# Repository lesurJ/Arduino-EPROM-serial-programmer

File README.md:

# Arduino-EPROM-serial-programmer

A project to program vintage EPROMs with modern Python and Arduino.

/!\ Work in progress. New version will include voltage regulators to generate the required programming voltages.

## Introduction

EPROMs are found in many old devices (scopes, data logger, computer). They are very good at long term data retention. And the good thing is they can be erased and re-programmed easily (with a bit of hardware).

Unfortunately, the devices for reading and programming EPROMs are usually expensive as they are universal: they can program almost all EPROMs. I really don't need such universal programmers as I use EPROMs for my hobby and I have only a few different types of EPROM.

## Description

A serial connection is opened between the computer and the arduino. This connection is used to transfer commands (read or write) and data (memory contents or machine code).

The circuit schematic is located [here](EPROM_FLASHER/Schematic.pdf).
It is based on an Arduino Nano, two 8-bit serial-in parallel-out shift registers (ref. 74HC595) and some passive components (condensator, 3 capacitors, 3 switches). Two soldering pads are present for powering the "program pin" of the EPROMs during a write operation.

The address lines of the EPROMs are driven by the shift registers whereas their data lines are driven by 8 Arduino pins.

## Installation

* Flash the [arduino program](arduino_programmer/arduino_programmer.ino) into the Arduino Nano. Use the Arduino IDE for this.
* Get yourself the PCB. You can directly upload the [zip file](EPROM_FLASHER/GERBER/EPROM_FLASHER.zip) to PCB production services.
* Solder the components on the PCB.
* Install a SINGLE EPROM on the board.

## Usage

* Connect the Arduino to the computer.
* For reading the EPROM run

```sh
python3 main.py -t X
```

where **X** is the memory type code (see [supported EPROMs](#supported-eproms)). The EPROM contents will be written in the file [epromContents_before.txt](epromContents_before.txt).

* For programming the EPROM run

```python
python3 main.py -t X -f path-to-the-machine-code-txt
```

where **X** is the memory type code (see [supported EPROMs](#supported-eproms)) and the path is indicating where you machine code is located.
Before programming, the program will pause and ask you to apply the programming voltage on the external supply pad. It will resume once you press the ENTER key.

## Example

A machine code example is located [here](programs/machineCode.txt). It is not a binary file but a txt files containing the program bytes on separate lines.

&rarr; If I want to read the contents of a NEC 2732D EPROM, I run

```sh
python3 main.py -t 32
```

&rarr; If I want to write the program [programs/machineCode.txt](programs/machineCode.txt) in the NEC 2732D EPROM, I run

```sh
python3 main.py -t 32 -f programs/machineCode.txt
```

I can see the contents of the EPROM in the file [epromContents_before.txt](epromContents_before.txt).

## Supported EPROMs

|EPROM|memory code|Memory Size [bytes]|
|---|---|---|
|27x16|16|2048|
|27x32|32|4096|
|27x64|64|8192|
|27x128|128|16384|
|27x256|256|32768|
|27x512|512|65536|

## Warning

DO NOT HOT-SWAP EPROM!

READ CAREFULLY THE DATASHEET FOR YOUR EPROM TO CHECK THE PROGRAMMING PROCEDURE AND VOLTAGE!

## Note

This project was made with components I had laying around. I didn't have a ZIF (Zero Insertion Force) socket for the EPROMs and this is the reason why I used 6 different sockets.

To keep the board simple, the programming voltage is not generated on the board, but  by an external power supply whose wires are attached to the power supply terminals.

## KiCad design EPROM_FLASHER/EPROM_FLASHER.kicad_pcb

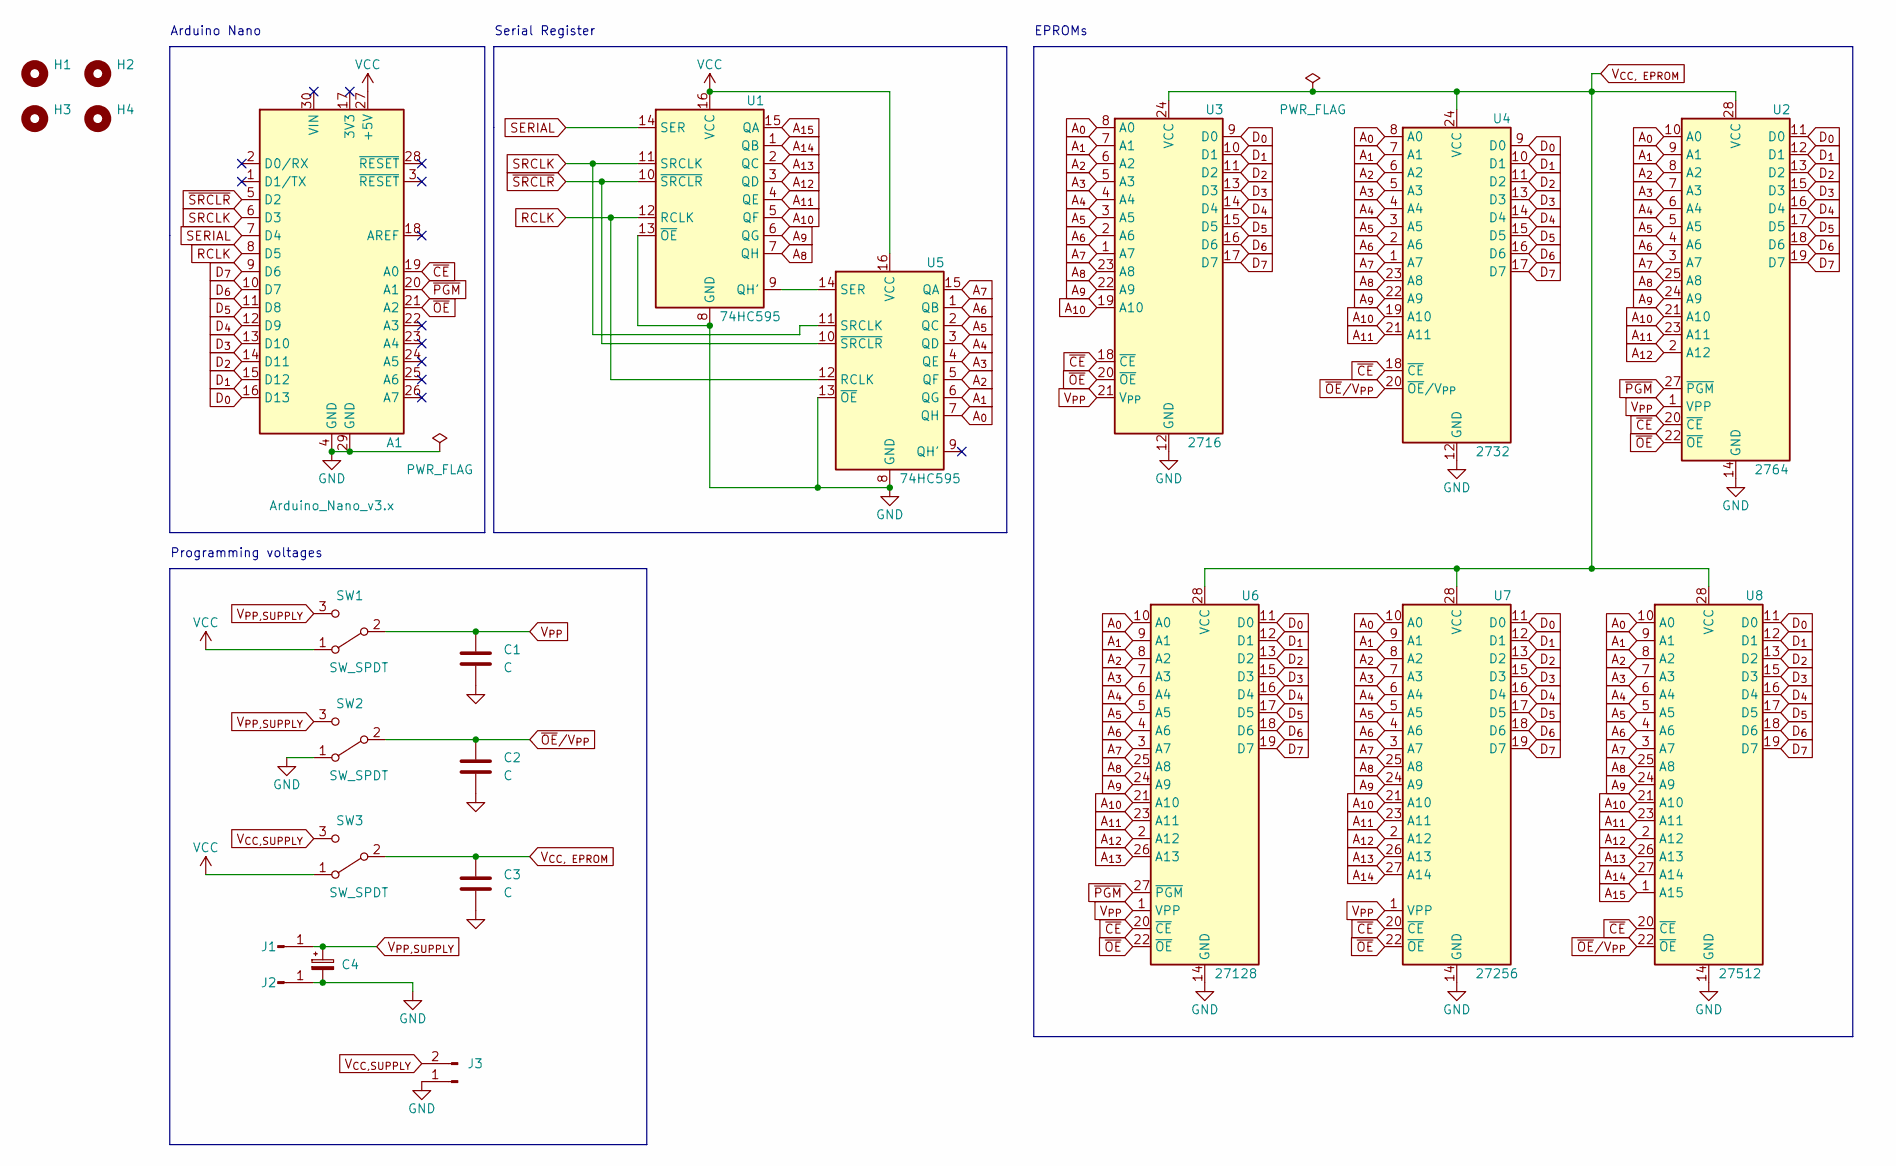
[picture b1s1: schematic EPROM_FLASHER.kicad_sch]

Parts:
A1: Arduino_Nano_v3.x; Arduino_Nano
C1, C2, C3: C; C_Disc_D9.0mm_W2.5mm_P5.00mm
C4: C_Polarized_Small; CP_Radial_D8.0mm_P3.50mm
H1, H2, H3, H4: MountingHole; MountingHole_2.2mm_M2
J1, J2: Conn_01x01_Male; TestPoint_Pad_4.0x4.0mm
J3: Conn_01x02_Male; PinHeader_1x02_P2.54mm_Vertical
SW1, SW2, SW3: SW_SPDT; SPDT_p2.54mm
U1, U5: 74HC595; DIP-16_W7.62mm
U2: 2764; DIP-28_W15.24mm
U3: 2716; DIP-24_W15.24mm
U4: 2732; DIP-24_W15.24mm
U6: 27128; DIP-28_W15.24mm
U7: 27256; DIP-28_W15.24mm
U8: 27512; DIP-28_W15.24mm

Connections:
A_{0}: U2.10 (A0), U3.8 (A0), U4.8 (A0), U5.7 (QH), U6.10 (A0), U7.10 (A0), U8.10 (A0)
A_{1}: U2.9 (A1), U3.7 (A1), U4.7 (A1), U5.6 (QG), U6.9 (A1), U7.9 (A1), U8.9 (A1)
A_{2}: U2.8 (A2), U3.6 (A2), U4.6 (A2), U5.5 (QF), U6.8 (A2), U7.8 (A2), U8.8 (A2)
A_{3}: U2.7 (A3), U3.5 (A3), U4.5 (A3), U5.4 (QE), U6.7 (A3), U7.7 (A3), U8.7 (A3)
A_{4}: U2.6 (A4), U3.4 (A4), U4.4 (A4), U5.3 (QD), U6.6 (A4), U7.6 (A4), U8.6 (A4)
A_{5}: U2.5 (A5), U3.3 (A5), U4.3 (A5), U5.2 (QC), U6.5 (A5), U7.5 (A5), U8.5 (A5)
A_{6}: U2.4 (A6), U3.2 (A6), U4.2 (A6), U5.1 (QB), U6.4 (A6), U7.4 (A6), U8.4 (A6)
A_{7}: U2.3 (A7), U3.1 (A7), U4.1 (A7), U5.15 (QA), U6.3 (A7), U7.3 (A7), U8.3 (A7)
A_{8}: U1.7 (QH), U2.25 (A8), U3.23 (A8), U4.23 (A8), U6.25 (A8), U7.25 (A8), U8.25 (A8)
A_{9}: U1.6 (QG), U2.24 (A9), U3.22 (A9), U4.22 (A9), U6.24 (A9), U7.24 (A9), U8.24 (A9)
A_{10}: U1.5 (QF), U2.21 (A10), U3.19 (A10), U4.19 (A10), U6.21 (A10), U7.21 (A10), U8.21 (A10)
A_{11}: U1.4 (QE), U2.23 (A11), U4.21 (A11), U6.23 (A11), U7.23 (A11), U8.23 (A11)
A_{12}: U1.3 (QD), U2.2 (A12), U6.2 (A12), U7.2 (A12), U8.2 (A12)
A_{13}: U1.2 (QC), U6.26 (A13), U7.26 (A13), U8.26 (A13)
A_{14}: U1.1 (QB), U7.27 (A14), U8.27 (A14)
A_{15}: U1.15 (QA), U8.1 (A15)
D_{0}: A1.16 (D13), U2.11 (D0), U3.9 (D0), U4.9 (D0), U6.11 (D0), U7.11 (D0), U8.11 (D0)
D_{1}: A1.15 (D12), U2.12 (D1), U3.10 (D1), U4.10 (D1), U6.12 (D1), U7.12 (D1), U8.12 (D1)
D_{2}: A1.14 (D11), U2.13 (D2), U3.11 (D2), U4.11 (D2), U6.13 (D2), U7.13 (D2), U8.13 (D2)
D_{3}: A1.13 (D10), U2.15 (D3), U3.13 (D3), U4.13 (D3), U6.15 (D3), U7.15 (D3), U8.15 (D3)
D_{4}: A1.12 (D9), U2.16 (D4), U3.14 (D4), U4.14 (D4), U6.16 (D4), U7.16 (D4), U8.16 (D4)
D_{5}: A1.11 (D8), U2.17 (D5), U3.15 (D5), U4.15 (D5), U6.17 (D5), U7.17 (D5), U8.17 (D5)
D_{6}: A1.10 (D7), U2.18 (D6), U3.16 (D6), U4.16 (D6), U6.18 (D6), U7.18 (D6), U8.18 (D6)
D_{7}: A1.9 (D6), U2.19 (D7), U3.17 (D7), U4.17 (D7), U6.19 (D7), U7.19 (D7), U8.19 (D7)
GND: A1.4 (GND), A1.29 (GND), C1.2, C2.2, C3.2, C4.2, J2.1, J3.1, SW2.1 (A), U1.8 (GND), U1.13 (~OE), U2.14 (GND), U3.12 (GND), U4.12 (GND), U5.8 (GND), U5.13 (~OE), U6.14 (GND), U7.14 (GND), U8.14 (GND)
unnamed: U1.9 (QH'), U5.14 (SER)
RCLK: A1.8 (D5), U1.12 (RCLK), U5.12 (RCLK)
SERIAL: A1.7 (D4), U1.14 (SER)
SRCLK: A1.6 (D3), U1.11 (SRCLK), U5.11 (SRCLK)
VCC: A1.27 (+5V), SW1.1 (A), SW3.1 (A), U1.16 (VCC), U5.16 (VCC)
V_{CC, EPROM}: C3.1, SW3.2 (B), U2.28 (VCC), U3.24 (VCC), U4.24 (VCC), U6.28 (VCC), U7.28 (VCC), U8.28 (VCC)
V_{CC,SUPPLY}: J3.2, SW3.3 (C)
V_{PP,SUPPLY}: C4.1, J1.1, SW1.3 (C), SW2.3 (C)
V_{PP}: C1.1, SW1.2 (B), U2.1 (VPP), U3.21 (V_{PP}), U6.1 (VPP), U7.1 (VPP)
~CE: A1.19 (A0), U2.20 (~CE), U3.18 (~CE), U4.18 (~CE), U6.20 (~CE), U7.20 (~CE), U8.20 (~CE)
~OE: A1.21 (A2), U2.22 (~OE), U3.20 (~OE), U6.22 (~OE), U7.22 (~OE)
~OE/V_{PP}: C2.1, SW2.2 (B), U4.20 (~OE/V_{PP}), U8.22 (~OE)
~PGM: A1.20 (A1), U2.27 (~PGM), U6.27 (~PGM)
~SRCLR: A1.5 (D2), U1.10 (~SRCLR), U5.10 (~SRCLR)

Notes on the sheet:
EPROMs
Serial Register
Programming voltages
Arduino Nano

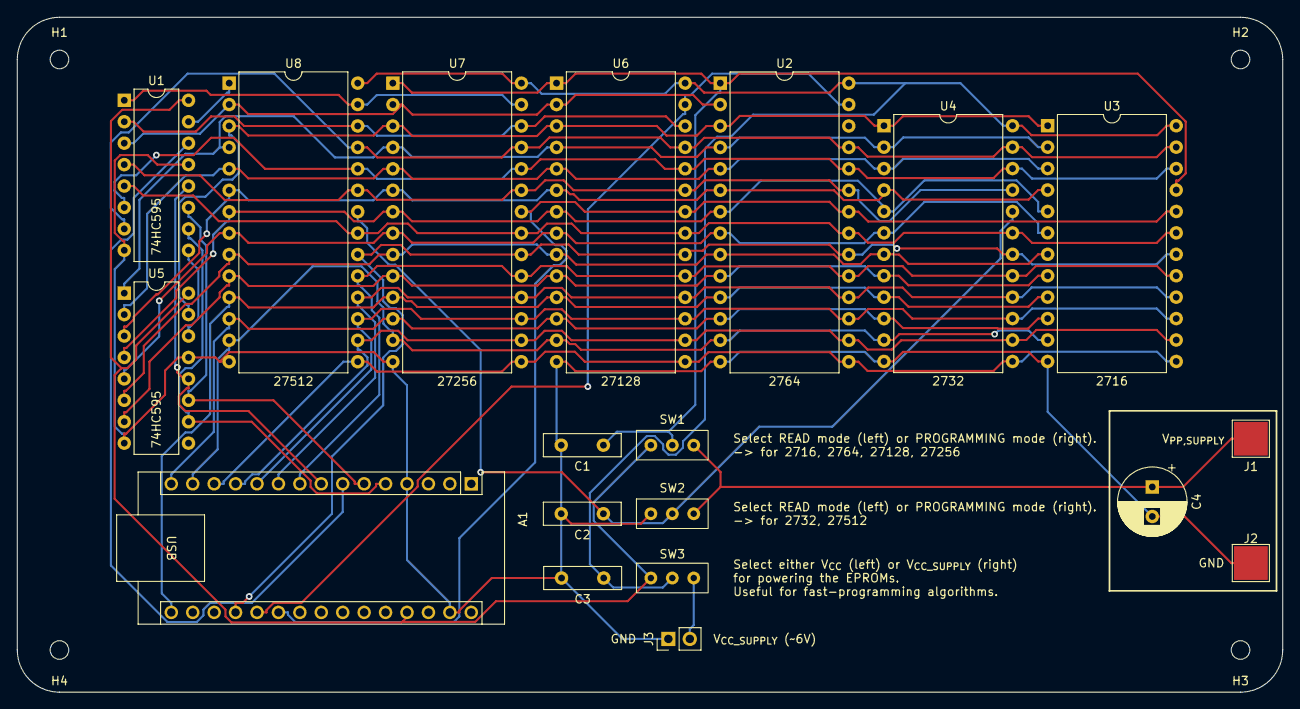
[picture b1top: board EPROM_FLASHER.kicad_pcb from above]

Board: 2 copper layers, 150.0 x 80.0 mm, 23 parts (0 on the bottom side), 39 nets.

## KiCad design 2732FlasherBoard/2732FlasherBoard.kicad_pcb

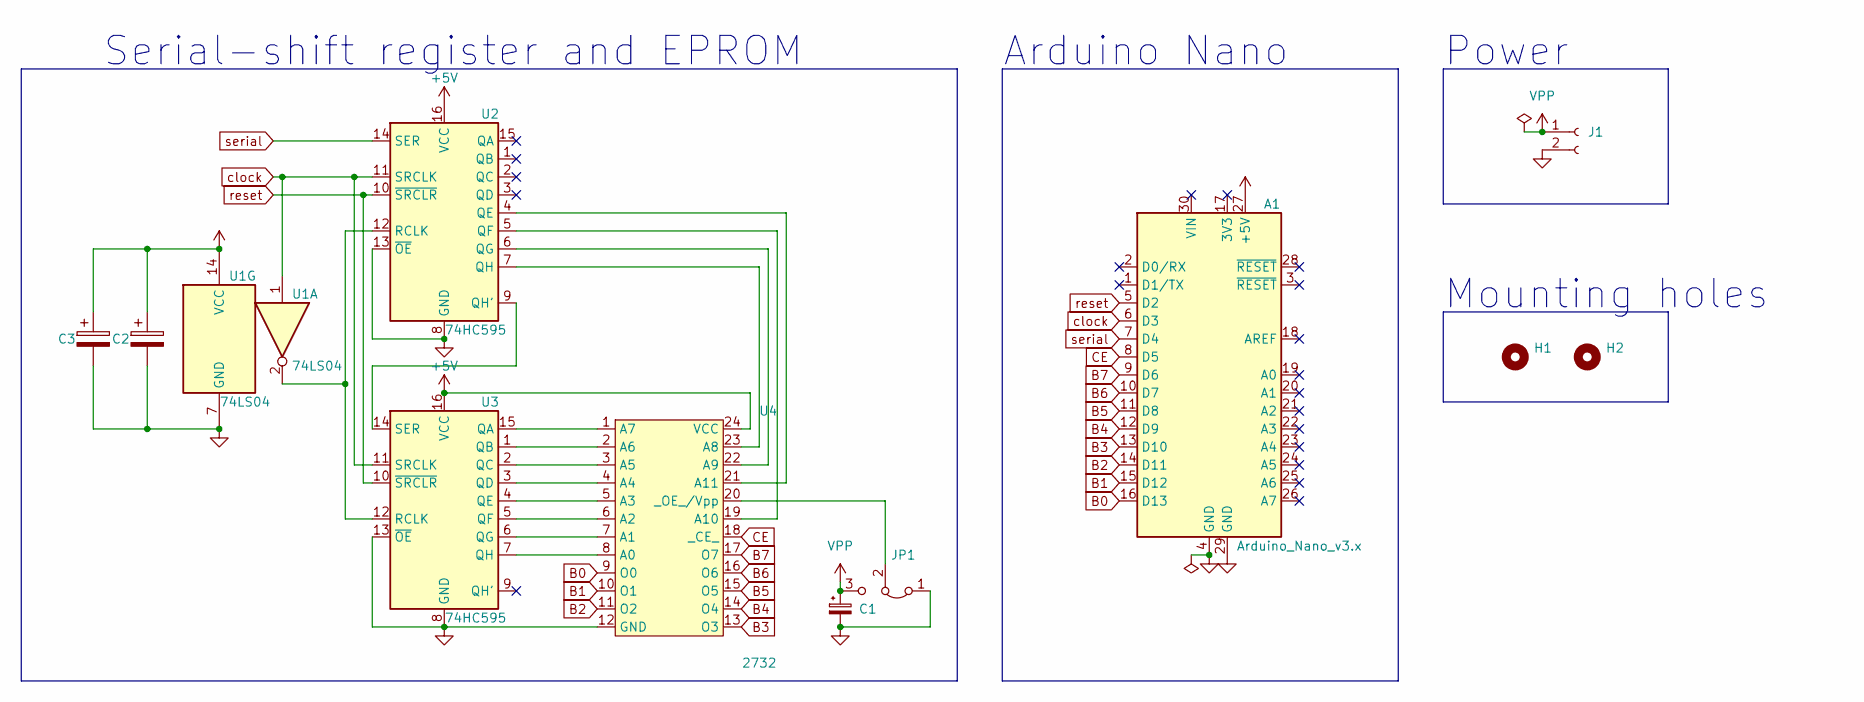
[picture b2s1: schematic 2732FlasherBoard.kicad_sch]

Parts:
A1: Arduino_Nano_v3.x; Arduino_Nano
C1: C_Polarized_Small; CP_Radial_D5.0mm_P2.00mm
C2, C3: C_Polarized; CP_Radial_D8.0mm_P3.50mm
H1, H2: MountingHole; MountingHole_2.5mm
J1: Conn_01x02_Female; PinHeader_1x02_P2.54mm_Vertical
JP1: Jumper_3_Bridged12; PinHeader_1x03_P2.54mm_Vertical
U1: 74LS04; DIP-14_W7.62mm
U2, U3: 74HC595; DIP-16_W7.62mm
U4: 2732; DIP-24_W15.24mm_Socket

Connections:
+5V: A1.27 (+5V), C2.1, C3.1, U1.14 (VCC), U2.16 (VCC), U3.16 (VCC), U4.24 (VCC)
B0: A1.16 (D13), U4.9 (O0)
B1: A1.15 (D12), U4.10 (O1)
B2: A1.14 (D11), U4.11 (O2)
B3: A1.13 (D10), U4.13 (O3)
B4: A1.12 (D9), U4.14 (O4)
B5: A1.11 (D8), U4.15 (O5)
B6: A1.10 (D7), U4.16 (O6)
B7: A1.9 (D6), U4.17 (O7)
CE: A1.8 (D5), U4.18 (_CE_)
GND: A1.4 (GND), A1.29 (GND), C1.2, C2.2, C3.2, J1.2, JP1.1 (A), U1.7 (GND), U2.8 (GND), U2.13 (~OE), U3.8 (GND), U3.13 (~OE), U4.12 (GND)
unnamed: JP1.2 (C), U4.20 (_OE_/Vpp)
unnamed: U1.2, U2.12 (RCLK), U3.12 (RCLK)
unnamed: U2.4 (QE), U4.21 (A11)
unnamed: U2.5 (QF), U4.19 (A10)
unnamed: U2.6 (QG), U4.22 (A9)
unnamed: U2.7 (QH), U4.23 (A8)
unnamed: U2.9 (QH'), U3.14 (SER)
unnamed: U3.1 (QB), U4.2 (A6)
unnamed: U3.2 (QC), U4.3 (A5)
unnamed: U3.3 (QD), U4.4 (A4)
unnamed: U3.4 (QE), U4.5 (A3)
unnamed: U3.5 (QF), U4.6 (A2)
unnamed: U3.6 (QG), U4.7 (A1)
unnamed: U3.7 (QH), U4.8 (A0)
unnamed: U3.15 (QA), U4.1 (A7)
VPP: C1.1, J1.1, JP1.3 (B)
clock: A1.6 (D3), U1.1, U2.11 (SRCLK), U3.11 (SRCLK)
reset: A1.5 (D2), U2.10 (~SRCLR), U3.10 (~SRCLR)
serial: A1.7 (D4), U2.14 (SER)

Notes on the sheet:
Arduino Nano
Power
Mounting holes
Serial-shift register and EPROM

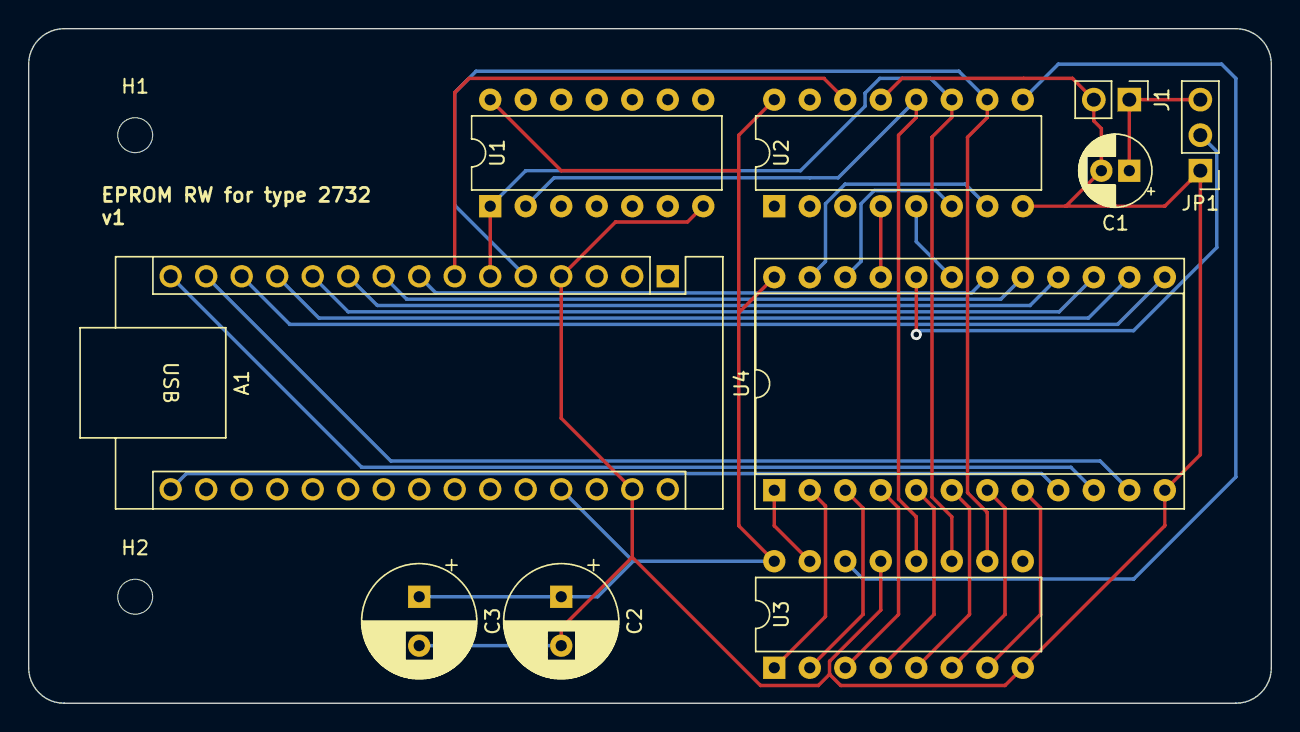
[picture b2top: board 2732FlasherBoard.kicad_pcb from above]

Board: 2 copper layers, 88.9 x 48.3 mm, 12 parts (0 on the bottom side), 30 nets.

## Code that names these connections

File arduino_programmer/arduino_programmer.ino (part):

const int nSRCLR_pin = 2;
const int SRCLK_pin = 3;
const int SERIAL_pin = 4;
const int RCLK_pin = 5;
const int msb_pin = 6;
const int lsb_pin = 13;

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
void setAddress(long address)
{
    digitalWrite(RCLK_pin, LOW);
    shiftOut(SERIAL_pin, SRCLK_pin, LSBFIRST, (byte)address);
    shiftOut(SERIAL_pin, SRCLK_pin, LSBFIRST, address >> 8);
    digitalWrite(RCLK_pin, HIGH);
    delayMicroseconds(1); // typical access time is 200ns for EPROM
}

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{
    // timing as specified in the datasheet
    const int tDS_us = 2;  // data setup time
    const int tPW_ms = 1;  // PGM pulse width
    const int tDH_us = 2;  // data hold time
    const int tOES_us = 2; // output enable setup time
    const int tOE_us = 2;  // data valid from output enable
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{
    // timing as specified in the datasheet
    const unsigned int tDS_us = 2;  // data setup time
    const unsigned long tPW_ms = 1; // PGM pulse width
    const unsigned int tDH_us = 2;  // data hold time
    const unsigned int tOES_us = 2; // output enable setup time
    const unsigned int tOE_us = 2;  // data valid from output enable
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{
    // timing as specified in the datasheet
    const unsigned int tDS_us = 2;   // data setup time
    const unsigned int tPW_us = 100; // PGM pulse width
    const unsigned int tDH_us = 2;   // data hold time
    const unsigned int tOES_us = 2;  // output enable setup time
    const unsigned int tOE_us = 1;   // data valid from output enable
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    Serial.begin(baudrate);

    pinMode(nSRCLR_pin, OUTPUT);
    pinMode(SRCLK_pin, OUTPUT);
    pinMode(SERIAL_pin, OUTPUT);
    pinMode(RCLK_pin, OUTPUT);
    pinMode(nCE_PIN, OUTPUT);
    pinMode(nPGM_PIN, OUTPUT);
    pinMode(nOE_PIN, OUTPUT);
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
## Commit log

2023-01-26 moved machineCode file to new folder
2023-01-26 connection to serial is now in a try-except
2023-01-26 added argparse + formatted code
2023-02-01 changed gitignore for epromContents
2023-02-01 machine code file is optional, when not provided, eprom contents are simply extracted
2023-02-01 fixed bug when program size was smaller than chunksize
2023-04-29 auto detect serial port + blacked
2023-05-21 added Kicad project
2023-05-21 added pdf
2023-09-21 update gitignore
2023-09-21 updated txt files
2023-09-21 new arduino program, handle different memory type
2023-09-21 remove unecessary sleep
2023-09-21 changed keyword, fixed bug related to program size (now passed to function); pin levels for each eprom type, added setup time delay
2023-09-21 changed memory_size and program_size to long type (bug: memory size > 32765 bytes won't be represented correctly in an int)
2023-09-22 improved code: removed serialConnector payload, memory is read by chunk in order for the script to display elapsed time, cleaned main
2023-09-22 added last version of pcb
2023-09-28 renamed variable chunk_index and chunk_addr to data_index and data_addr
2023-09-28 added readMemoryAtAddress function to help with fast rogramming algorithm
2023-09-28 renamde chunk_buffer to data_buffer
2023-09-28 added quickPro algorithm for fujitsu eprom type 64 and higher
2023-09-29 added changeDataPin function for easier program verification, cleaned code
2023-09-29 updated gitignore
2023-09-29 functions have been splitted for easier use (useful for fast programming algorithm)
2023-09-30 program exits when no tty.usbserial port is found
2023-09-30 added QuickPro, FastProg and PrestoII programming algorithm. Only the latter is working for the corresponding ST 256 EPROMs
